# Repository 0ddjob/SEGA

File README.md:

# Sega Projects
The Sega Saturn was my first console (apart from my dad's Atari 2600), so has a special place in memory.<br>

## Sega Mark III
### [RGB amplifier](/Mark_III)<br>
An internal & external RGB video signal amplifier.<br>

## Sega SC-3000
I did start working on a homebrew SC-3000 ... but an already, far-superior [version](https://github.com/barbeque/sg1000) based on the SG-1000 has already been created.  You just need to add an SK-1100 keyboard ... DIY version also under development.<br>

## Sega Saturn
### [Windows Communication Cable](/Saturn/Windows_Communication_Cable)<br>

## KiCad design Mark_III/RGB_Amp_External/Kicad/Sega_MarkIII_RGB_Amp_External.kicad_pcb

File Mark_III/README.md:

# Sega Mark III RGB Amplifier
An internal & external RGB amplifier board for the Sega Mark III RGB output.<br>

The RGB output is apparently a bit dim so one solution is to use a THS7314D (or similar) video amplifier to boost the output level.  This part is surface mount so I've designed the whole board to be surface mount.<br>

Based on design & ideas by [にがMSX](http://niga2.sytes.net/msx/mk3.html)<br>

This implementation not yet tested.  Will update once test boards have been fabricated & tested.<br>

Design uses:<br>
- 6 x 75Ω (0805) resistors
- 1 x 100Ω (0805) resistor
- 1 x 100nF (0805) capacitor
- 1 x THS7314D video amplifier (6dB gain)
- 6-pin header for RGBS+power input (internal)
- 5-pin header for RGBS+ground output (internal)
- DIN-8 connector for input (external)
- DE15 HD connector for VGA output (external)
- RCA phono jack for composite video output (external)
- 3.5mm socket for audio output (external)

## Status
22-Nov-2025: completely re-designed the PCB

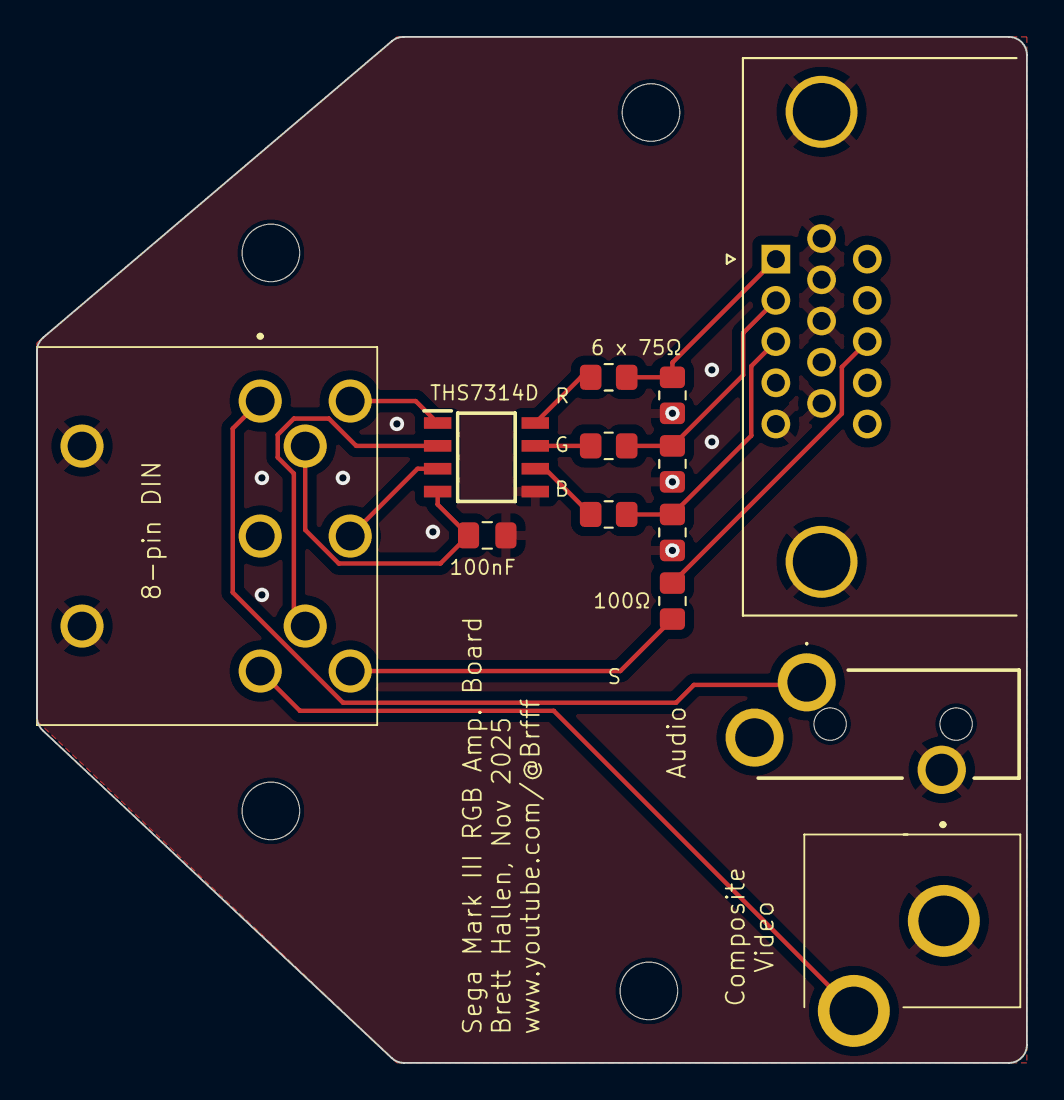
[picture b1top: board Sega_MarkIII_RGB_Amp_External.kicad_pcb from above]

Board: 2 copper layers, 55.0 x 57.0 mm, 17 parts (0 on the bottom side), 15 nets.

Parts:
C1: 100nF; C_0805_2012Metric_Pad1.18x1.45mm_HandSolder
H1, H2, H3, H4: MountingHole; MountingHole_3.2mm_M3_DIN965
IC1: THS7314D; SOIC127P600X175-8N
J1: RGBS Input; 6710801
J2: VGA Out; DSUB-15-HD_Socket_Horizontal_P2.29x2.54mm_EdgePinOffset8.35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
J3: Audio; SJ3350820BTR
J4: Video Out; FC68371
R1, R2, R3, R5, R6, R7: 75Ω; R_0805_2012Metric_Pad1.20x1.40mm_HandSolder
R4: 100Ω; R_0805_2012Metric_Pad1.20x1.40mm_HandSolder

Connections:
+5V: C1.2, IC1.4 (VS+), J1.4
AUDIO: J1.1, J3.2 (TIP)
BLUE_{IN}: IC1.3 (CH.3_IN), J1.8
BLUE_{OUT}: J2.3, R3.1, R5.1
C.SYNC_{IN}: J1.7, R4.2
C.SYNC_{OUT}: J2.13, R4.1
GND: C1.1, IC1.5 (GND), J1.2, J1.MH1, J1.MH2, J2.0, J2.5, J2.6, J2.7, J2.8, J2.10, J3.5 (RING), J4.1 (SLEEVE), R5.2, R6.2, R7.2
GREEN_{IN}: IC1.2 (CH.2_IN), J1.5
GREEN_{OUT}: J2.2, R2.1, R6.1
unnamed: IC1.8 (CH.1_OUT), R1.2
unnamed: IC1.7 (CH.2_OUT), R2.2
unnamed: IC1.6 (CH.3_OUT), R3.2
RED_{IN}: IC1.1 (CH.1_IN), J1.6
RED_{OUT}: J2.1, R1.1, R7.1
VIDEO: J1.3, J4.3 (TIP_SWITCH)

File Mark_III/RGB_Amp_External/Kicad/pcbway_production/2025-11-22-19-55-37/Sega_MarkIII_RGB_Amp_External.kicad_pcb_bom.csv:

Designator,Quantity,Value,Footprint,Package,MPN,DNP,Mount_Type,Height,Manufacturer_Name,Mouser Part Number,Mouser Price/Stock,Description
C1,1,100nF,C_0805_2012Metric_Pad1.18x1.45mm_HandSolder,,,,smt,,,,,
IC1,1,THS7314D,SOIC127P600X175-8N,,THS7314DR,,smt,1.75,Texas Instruments,595-THS7314DR,https://www.mouser.co.uk/ProductDetail/Texas-Instruments/THS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,
J2,1,VGA Out,DSUB-15-HD_Socket_Horizontal_P2.29x2.54mm_EdgePinOffset8.35mm_Housed_MountingHolesOffset10.89mm,,,,tht,,,,,"15-pin D-SUB connector, socket (female), High density (3 columns), Triple Row, Generic, VGA-connector, Mounting Hole"
J3,1,Audio,SJ3350820BTR,,SJ3-350820B-TR,,tht,5.3,Same Sky,179-SJ3-350820B-TR,https://www.mouser.co.uk/ProductDetail/Same-Sky/SJ3-350820B-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,"3.5 mm Stereo Jack, Through Hole, 2 Conductors, 1 Internal Switches,  Tape & Reel Packaging"
J4,1,RGBS Input,6710801,,671-0801,,tht,19.5,DELTRON COMPONENTS,,,"Deltron 8 Pole Right Angle Din Socket Socket, 2A, 100 V ac, Lockable"
J5,1,Video Out,FC68371,,FC68371,,tht,14,CLIFF ELECTRONIC COMPONENTS,,,Socket; RCA; female; angled 90; THT; nickel plated; Marker: black
"R1, R2, R3, R5, R6, R7",6,75Ω,R_0805_2012Metric_Pad1.20x1.40mm_HandSolder,,,,smt,,,,,
R4,1,100Ω,R_0805_2012Metric_Pad1.20x1.40mm_HandSolder,,,,smt,,,,,

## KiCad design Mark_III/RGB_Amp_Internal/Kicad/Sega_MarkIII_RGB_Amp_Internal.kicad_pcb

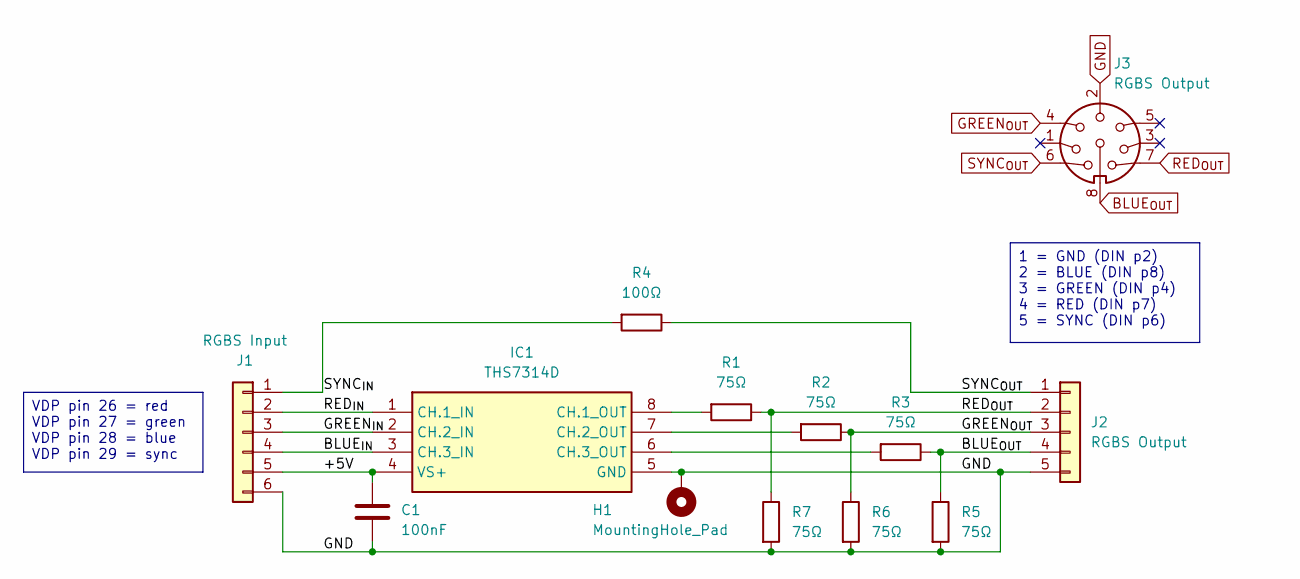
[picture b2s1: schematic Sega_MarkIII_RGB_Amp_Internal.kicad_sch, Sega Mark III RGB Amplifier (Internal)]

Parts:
C1: 100nF; C_0805_2012Metric_Pad1.18x1.45mm_HandSolder
H1: MountingHole_Pad; MountingHole_3.2mm_M3_DIN965_Pad_TopBottom
IC1: THS7314D; SOIC127P600X175-8N; Mouser Part Number 595-THS7314DR
J1: RGBS Input; PinHeader_1x06_P2.54mm_Horizontal
J2: RGBS Output; PinHeader_1x05_P2.54mm_Horizontal
J3: RGBS Output
R1, R2, R3, R5, R6, R7: 75Ω; R_0805_2012Metric_Pad1.20x1.40mm_HandSolder
R4: 100Ω; R_0805_2012Metric_Pad1.20x1.40mm_HandSolder

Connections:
/+5V: C1.2, IC1.4 (VS+), J1.5
/BLUE_{IN}: IC1.3 (CH.3_IN), J1.4
/GREEN_{IN}: IC1.2 (CH.2_IN), J1.3
/RED_{IN}: IC1.1 (CH.1_IN), J1.2
/SYNC_{IN}: J1.1, R4.2
BLUE_{OUT}: J2.4, R3.1, R5.1
GND: C1.1, H1.1, IC1.5 (GND), J1.6, J2.5, R5.2, R6.2, R7.2
GREEN_{OUT}: J2.3, R2.1, R6.1
unnamed: IC1.8 (CH.1_OUT), R1.2
unnamed: IC1.7 (CH.2_OUT), R2.2
unnamed: IC1.6 (CH.3_OUT), R3.2
RED_{OUT}: J2.2, R1.1, R7.1
SYNC_{OUT}: J2.1, R4.1

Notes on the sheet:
VDP pin 26 = red VDP pin 27 = green VDP pin 28 = blue VDP pin 29 = sync
1 = GND (DIN p2) 2 = BLUE (DIN p8) 3 = GREEN (DIN p4) 4 = RED (DIN p7) 5 = SYNC (DIN p6)

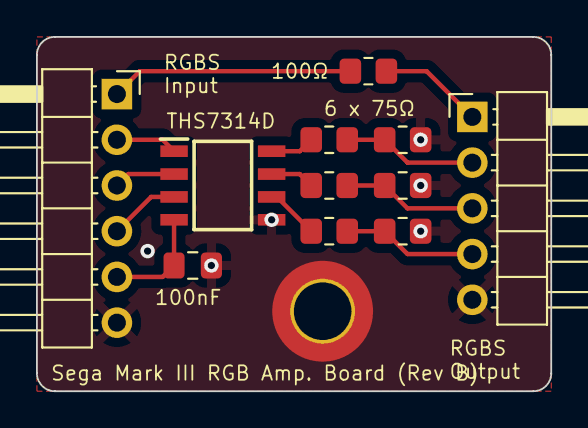
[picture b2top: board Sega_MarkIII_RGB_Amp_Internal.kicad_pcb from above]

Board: 2 copper layers, 28.6 x 19.7 mm, 12 parts (0 on the bottom side), 13 nets.

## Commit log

2023-09-15 Initial
2023-10-01 Removed SC-3000HB
2023-10-01 Renamed schematic PDF
2023-10-01 Saturn plug pinout
2023-10-01 Cleaned up JAP images so ENG translation a little better
2025-11-22 New PCB layout
2025-11-22 Minor 5V track re-route
2025-11-22 Refreshing design & repository
2025-11-22 Redesign PCB shape
